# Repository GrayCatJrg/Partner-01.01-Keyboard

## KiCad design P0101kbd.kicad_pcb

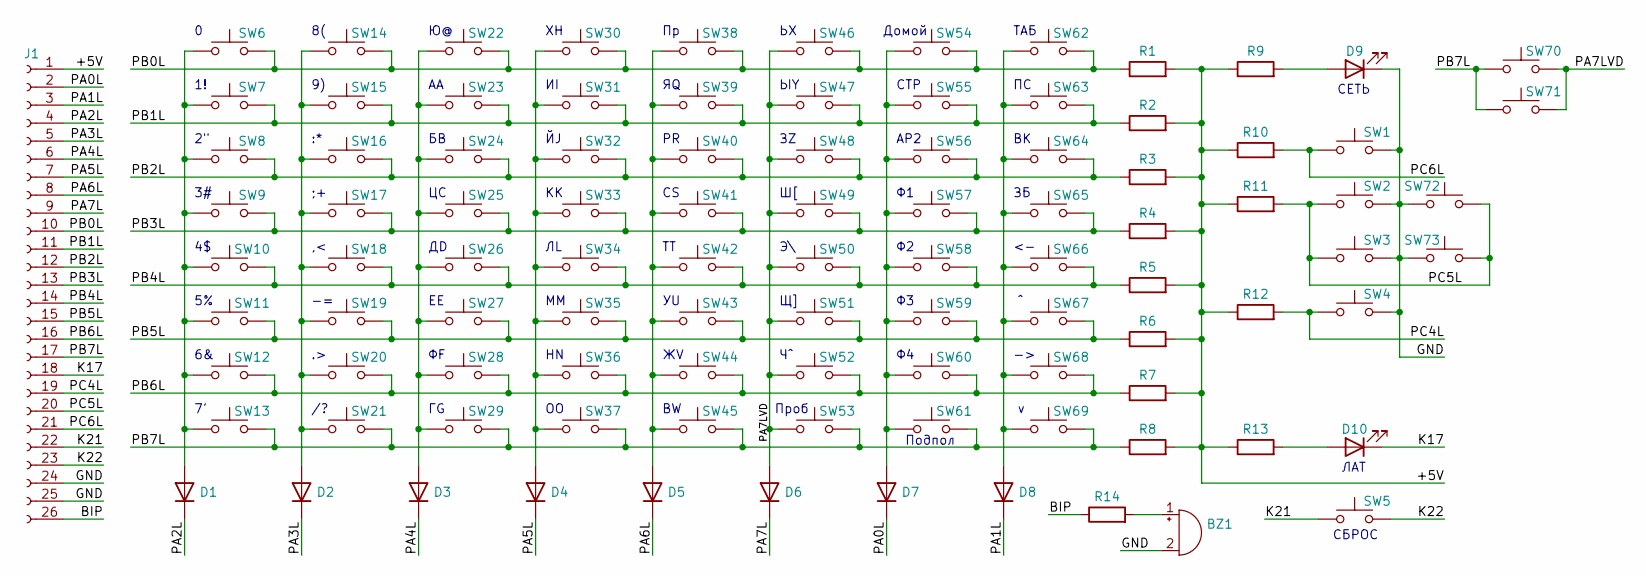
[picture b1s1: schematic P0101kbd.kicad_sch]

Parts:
BZ1: Buzzer; ZP1
D1, D2, D3, D4, D5, D6, D7, D8: 1N4148; D_SOD-323
D9, D10: LED; LED_D5.0mm
J1: Conn_01x26_Socket; PinSocket_1x30_P2.54mm_Horizontal_
R1, R2, R3, R4, R5, R6, R7, R8, R10, R11, R12: 10K; R_1206_3216Metric_Pad1.30x1.75mm_HandSolder
R9, R13: 330; R_1206_3216Metric_Pad1.30x1.75mm_HandSolder
R14: 120; R_1206_3216Metric_Pad1.30x1.75mm_HandSolder
SW1, SW4, SW5, SW22, SW23, SW24, SW25, SW26, SW27, SW28, SW29, SW30, SW31, SW32, SW33, SW34, SW35, SW36, SW37, SW38, SW39, SW40, SW41, SW42, SW43, SW44, SW45, SW46, SW47, SW48, SW49, SW50, SW51, SW52, SW54, SW55, SW56, SW57, SW58, SW59, SW60, SW61, SW62, SW63, SW64, SW65, SW66, SW67, SW68, SW69, SW70, SW71: SW_Push; SW_Cherry_MX_1.00u_Plate_
SW2, SW3, SW72, SW73: SW_Push; SW_Cherry_MX_1.25u_Plate_
SW6: 0; SW_Cherry_MX_1.00u_Plate_
SW7: 1!; SW_Cherry_MX_1.00u_Plate_
SW8: 2"; SW_Cherry_MX_1.00u_Plate_
SW9: 3#; SW_Cherry_MX_1.00u_Plate_
SW10: 4$; SW_Cherry_MX_1.00u_Plate_
SW11: 5%; SW_Cherry_MX_1.00u_Plate_
SW12: 6&; SW_Cherry_MX_1.00u_Plate_
SW13: 7'; SW_Cherry_MX_1.00u_Plate_
SW14: 8(; SW_Cherry_MX_1.00u_Plate_
SW15: 9); SW_Cherry_MX_1.00u_Plate_
SW16: :*; SW_Cherry_MX_1.00u_Plate_
SW17: ;+; SW_Cherry_MX_1.00u_Plate_
SW18: ,<; SW_Cherry_MX_1.00u_Plate_
SW19: -=; SW_Cherry_MX_1.00u_Plate_
SW20: .>; SW_Cherry_MX_1.00u_Plate_
SW21: /?; SW_Cherry_MX_1.00u_Plate_
SW53: SW_Push; SW_Cherry_MX_6.25u_Plate

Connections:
/+5V: J1.1, R1.2, R2.2, R3.2, R4.2, R5.2, R6.2, R7.2, R8.2, R9.1, R10.1, R11.1, R12.1, R13.1
/BIP: J1.26, R14.1
/GND: BZ1.2 (+), BZ1.G1, BZ1.G2, D9.1 (K), J1.24, J1.25, SW1.2, SW2.2, SW3.2, SW4.2, SW72.2, SW73.2; also elsewhere on the board
/K17: D10.1 (K), J1.18
/K21: J1.22, SW5.1
/K22: J1.23, SW5.2
/PA0L: D7.1 (K), J1.2
/PA1L: D8.1 (K), J1.3
/PA2L: D1.1 (K), J1.4
/PA3L: D2.1 (K), J1.5
/PA4L: D3.1 (K), J1.6
/PA5L: D4.1 (K), J1.7
/PA6L: D5.1 (K), J1.8
/PA7L: D6.1 (K), J1.9
/PA7LVD: D6.2 (A), SW46.1, SW47.1, SW48.1, SW49.1, SW50.1, SW51.1, SW52.1, SW53.1, SW70.1, SW71.1
/PB0L: J1.10, R1.1, SW6.2, SW14.2, SW22.2, SW30.2, SW38.2, SW46.2, SW54.2, SW62.2
/PB1L: J1.11, R2.1, SW7.2, SW15.2, SW23.2, SW31.2, SW39.2, SW47.2, SW55.2, SW63.2
/PB2L: J1.12, R3.1, SW8.2, SW16.2, SW24.2, SW32.2, SW40.2, SW48.2, SW56.2, SW64.2
/PB3L: J1.13, R4.1, SW9.2, SW17.2, SW25.2, SW33.2, SW41.2, SW49.2, SW57.2, SW65.2
/PB4L: J1.14, R5.1, SW10.2, SW18.2, SW26.2, SW34.2, SW42.2, SW50.2, SW58.2, SW66.2
/PB5L: J1.15, R6.1, SW11.2, SW19.2, SW27.2, SW35.2, SW43.2, SW51.2, SW59.2, SW67.2
/PB6L: J1.16, R7.1, SW12.2, SW20.2, SW28.2, SW36.2, SW44.2, SW52.2, SW60.2, SW68.2
/PB7L: J1.17, R8.1, SW13.2, SW21.2, SW29.2, SW37.2, SW45.2, SW53.2, SW61.2, SW69.2, SW70.2, SW71.2
/PC4L: J1.19, R12.2, SW4.1
/PC5L: J1.20, R11.2, SW2.1, SW3.1, SW72.1, SW73.1
/PC6L: J1.21, R10.2, SW1.1
unnamed: BZ1.1 (-), R14.2
unnamed: D1.2 (A), SW6.1, SW7.1, SW8.1, SW9.1, SW10.1, SW11.1, SW12.1, SW13.1
unnamed: D2.2 (A), SW14.1, SW15.1, SW16.1, SW17.1, SW18.1, SW19.1, SW20.1, SW21.1
unnamed: D3.2 (A), SW22.1, SW23.1, SW24.1, SW25.1, SW26.1, SW27.1, SW28.1, SW29.1
unnamed: D4.2 (A), SW30.1, SW31.1, SW32.1, SW33.1, SW34.1, SW35.1, SW36.1, SW37.1
unnamed: D5.2 (A), SW38.1, SW39.1, SW40.1, SW41.1, SW42.1, SW43.1, SW44.1, SW45.1
unnamed: D7.2 (A), SW54.1, SW55.1, SW56.1, SW57.1, SW58.1, SW59.1, SW60.1, SW61.1
unnamed: D8.2 (A), SW62.1, SW63.1, SW64.1, SW65.1, SW66.1, SW67.1, SW68.1, SW69.1
unnamed: D9.2 (A), R9.2
unnamed: D10.2 (A), R13.2

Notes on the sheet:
ЛАТ
СТР
СЕТЬ
Подпол
ТАБ
Домой
СБРОС
АР2
Проб

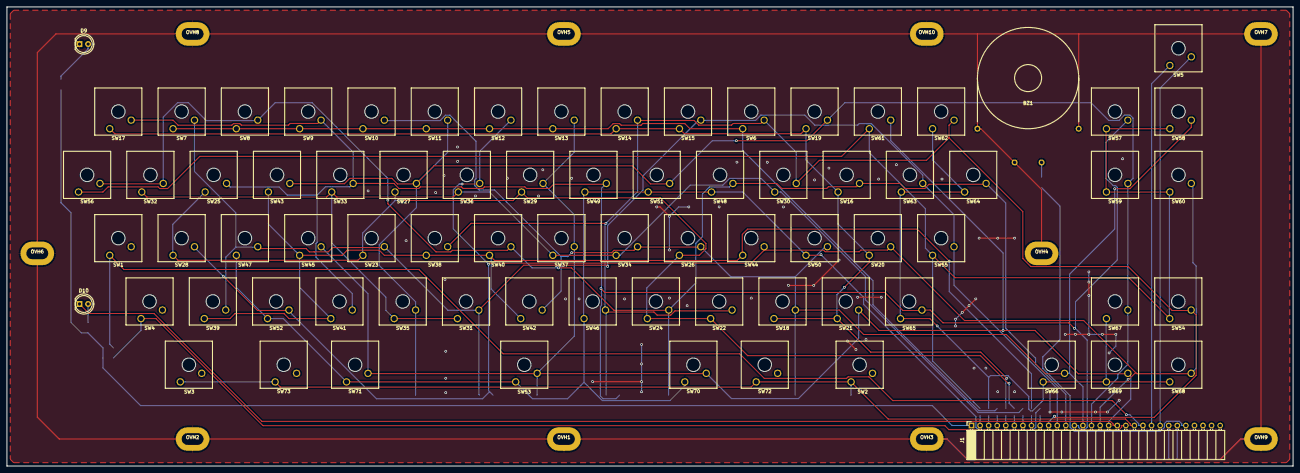
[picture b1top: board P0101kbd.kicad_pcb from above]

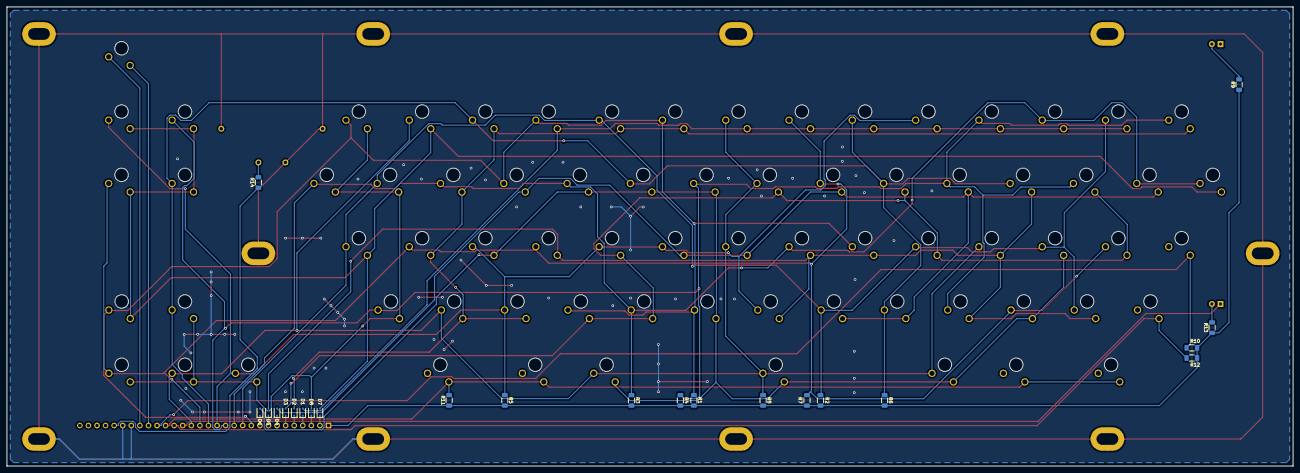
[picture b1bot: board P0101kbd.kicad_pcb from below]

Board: 2 copper layers, 381.0 x 136.0 mm, 109 parts (22 on the bottom side), 36 nets.

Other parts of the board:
OVH1, OVH2, OVH3, OVH4, OVH5, OVH6, OVH7, OVH8, OVH9, OVH10: OvHole

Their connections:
/GND: OVH1.1, OVH2.1, OVH3.1, OVH4.1, OVH5.1, OVH6.1, OVH7.1, OVH8.1, OVH9.1, OVH10.1; also elsewhere on the board

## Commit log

2023-10-07 Add files via upload
    Initial commit
2023-10-07 Create LICENSE
